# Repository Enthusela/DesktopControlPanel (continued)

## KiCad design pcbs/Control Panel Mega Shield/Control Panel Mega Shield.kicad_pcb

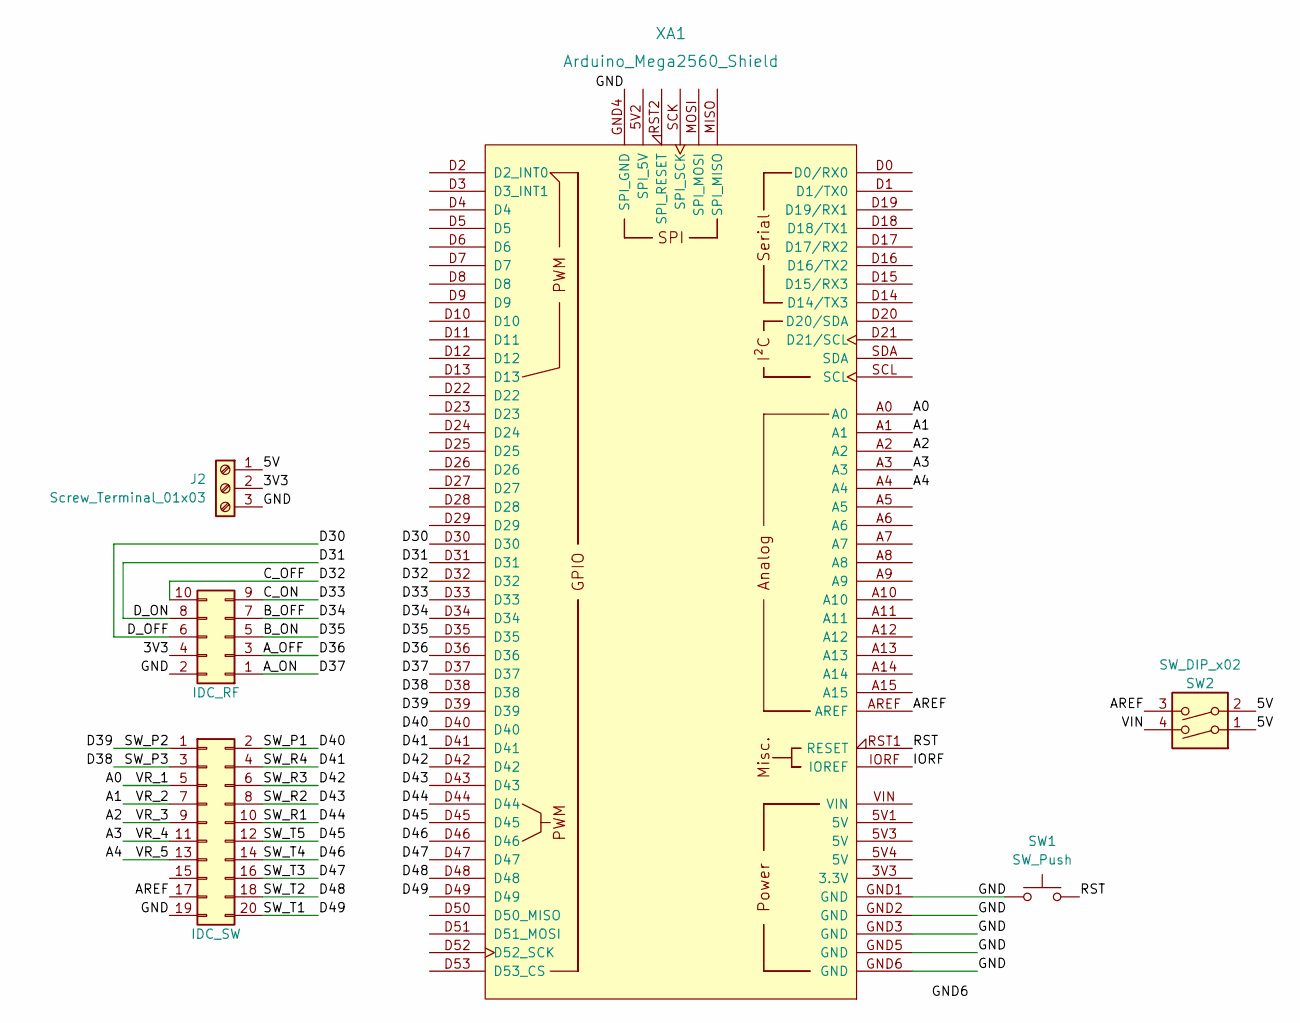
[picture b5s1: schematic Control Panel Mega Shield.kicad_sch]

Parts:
J1: IDC_SW; IDC-Header_2x10_P2.54mm_Vertical
J2: Screw_Terminal_01x03; TerminalBlock_bornier-3_P5.08mm
J3: IDC_RF; IDC-Header_2x05_P2.54mm_Vertical
SW1: SW_Push; SW_PUSH_6mm_H5mm
SW2: SW_DIP_x02; SW_DIP_SPSTx02_Slide_9.78x7.26mm_W7.62mm_P2.54mm
XA1: Arduino_Mega2560_Shield

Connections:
/3V3: J2.2, J3.4
/5V: J2.1, SW2.1, SW2.2
/A0: J1.5, XA1.A0
/A1: J1.7, XA1.A1
/A2: J1.9, XA1.A2
/A3: J1.11, XA1.A3
/A4: J1.13, XA1.A4
/AREF: J1.17, SW2.3, XA1.AREF
/A_OFF: J3.3, XA1.D36
/A_ON: J3.1, XA1.D37
/B_OFF: J3.7, XA1.D34
/B_ON: J3.5, XA1.D35
/C_OFF: J3.10, XA1.D32
/C_ON: J3.9, XA1.D33
/D30: J3.6, XA1.D30
/D31: J3.8, XA1.D31
/D38: J1.3, XA1.D38
/D39: J1.1, XA1.D39
/D40: J1.2, XA1.D40
/D41: J1.4, XA1.D41
/D42: J1.6, XA1.D42
/D43: J1.8, XA1.D43
/D44: J1.10, XA1.D44
/D45: J1.12, XA1.D45
/D46: J1.14, XA1.D46
/D47: J1.16, XA1.D47
/D48: J1.18, XA1.D48
/D49: J1.20, XA1.D49
/GND: J1.19, J2.3, J3.2, SW1.1, XA1.GND1 (GND), XA1.GND2 (GND), XA1.GND3 (GND), XA1.GND4 (SPI_GND), XA1.GND5 (GND), XA1.GND6 (GND)
/IORF: XA1.IORF (IOREF)
/RST: SW1.2, XA1.RST1 (RESET)
/VIN: SW2.4

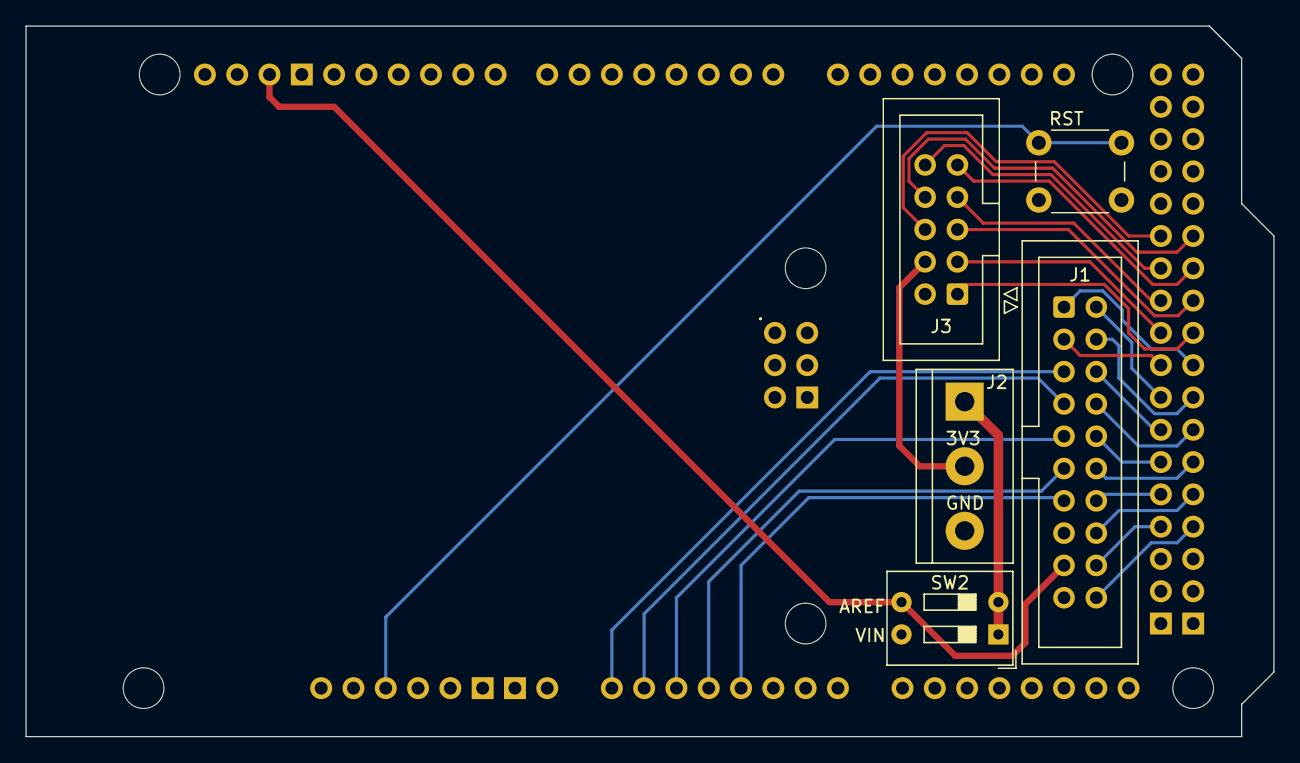
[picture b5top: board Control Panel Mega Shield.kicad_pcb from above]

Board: 2 copper layers, 98.1 x 55.9 mm, 6 parts (0 on the bottom side), 30 nets.

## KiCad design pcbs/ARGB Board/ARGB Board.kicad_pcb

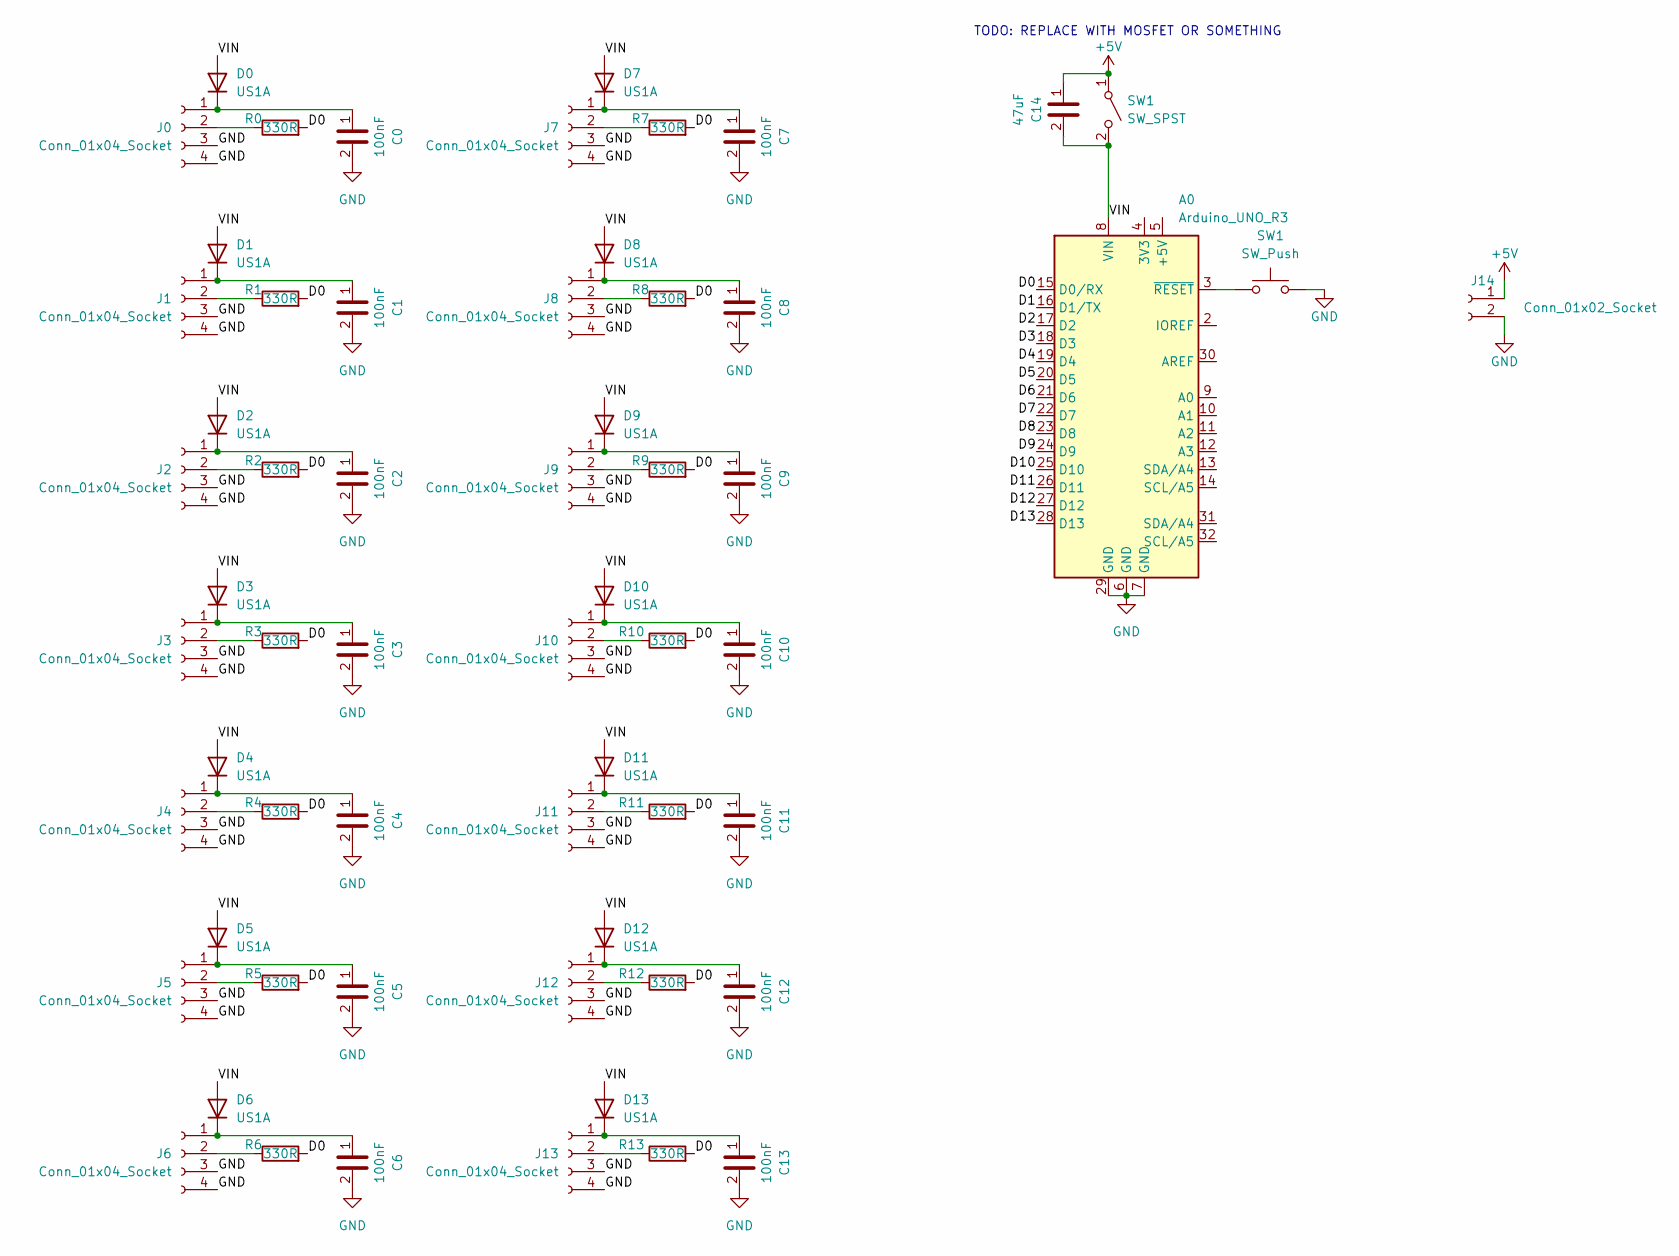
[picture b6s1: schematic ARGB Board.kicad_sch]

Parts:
A0: Arduino_UNO_R3; Arduino_UNO_R3_EdgeCuts
C0, C1, C2, C3, C4, C5, C6, C7, C8, C9, C10, C11, C12, C13: 100nF; C_0805_2012Metric_Pad1.18x1.45mm_HandSolder
C14: 47uF; CP_Radial_D6.3mm_P2.50mm
D0, D1, D2, D3, D4, D5, D6, D7, D8, D9, D10, D11, D12, D13: US1A; D_SMA
J0, J1, J2, J3, J4, J5, J6, J7, J8, J9, J10, J11, J12, J13: Conn_01x04_Socket; PinHeader_1x04_P2.54mm_Vertical
J14: Conn_01x02_Socket; TerminalBlock_bornier-2_P5.08mm
R0, R1, R2, R3, R4, R5, R6, R7, R8, R9, R10, R11, R12, R13: 330R; R_0805_2012Metric
SW1: SW_SPST; SW_E-Switch_EG1271_SPDT

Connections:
/D0: A0.15 (D0/RX), R0.2, R1.2, R2.2, R3.2, R4.2, R5.2, R6.2, R7.2, R8.2, R9.2, R10.2, R11.2, R12.2, R13.2
/D1: A0.16 (D1/TX)
/D2: A0.17 (D2)
/D3: A0.18 (D3)
/D4: A0.19 (D4)
/D5: A0.20 (D5)
/D6: A0.21 (D6)
/D7: A0.22 (D7)
/D8: A0.23 (D8)
/D9: A0.24 (D9)
/D10: A0.25 (D10)
/D11: A0.26 (D11)
/D12: A0.27 (D12)
/D13: A0.28 (D13)
unnamed: C0.1, D0.1 (K), J0.1
unnamed: C1.1, D1.1 (K), J1.1
unnamed: C2.1, D2.1 (K), J2.1
unnamed: C3.1, D3.1 (K), J3.1
unnamed: C4.1, D4.1 (K), J4.1
unnamed: C5.1, D5.1 (K), J5.1
unnamed: C6.1, D6.1 (K), J6.1
unnamed: C7.1, D7.1 (K), J7.1
unnamed: C8.1, D8.1 (K), J8.1
unnamed: C9.1, D9.1 (K), J9.1
unnamed: C10.1, D10.1 (K), J10.1
unnamed: C11.1, D11.1 (K), J11.1
unnamed: C12.1, D12.1 (K), J12.1
unnamed: C13.1, D13.1 (K), J13.1
unnamed: J0.2, R0.1
unnamed: J1.2, R1.1
unnamed: J2.2, R2.1
unnamed: J3.2, R3.1
unnamed: J4.2, R4.1
unnamed: J5.2, R5.1
unnamed: J6.2, R6.1
unnamed: J7.2, R7.1
unnamed: J8.2, R8.1
unnamed: J9.2, R9.1
unnamed: J10.2, R10.1
unnamed: J11.2, R11.1
unnamed: J12.2, R12.1
unnamed: J13.2, R13.1

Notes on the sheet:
TODO: REPLACE WITH MOSFET OR SOMETHING

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
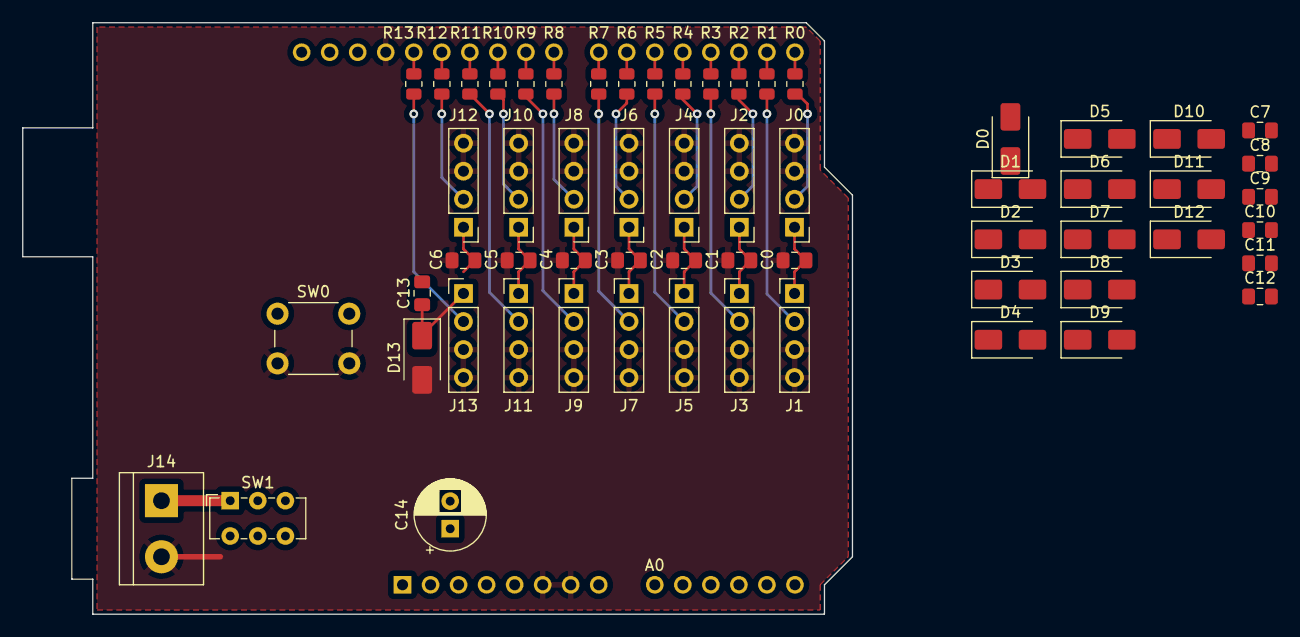
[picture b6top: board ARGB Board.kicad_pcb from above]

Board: 2 copper layers, 75.2 x 53.6 mm, 61 parts (1 on the bottom side), 33 nets.

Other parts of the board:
SW0: SW_Push; SW_PUSH_6mm_H5mm

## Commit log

2023-02-07 Initial commit. Running homepage pset website on local flask.
2023-02-16 Uploaded working files from Raspberry Pi. Webpage is ready for hosting.
2023-02-16 Added app.py and templates folder to staged changes.
2023-02-17 Added package-json files
2023-02-17 Added wordclock e-ink test code
2023-02-17 Added e-ink display wordclock test
2023-02-17 Converted wordclock from folder to submodule
2023-02-17 Updated wordclock files
2023-02-17 Untracked e-ink img folders
2023-02-17 Removed wordclock sub-module
2023-02-17 Added files from successful 7-color e-ink tests
2023-03-16 Bulk commit.
2023-03-17 Added motorised takeover
2023-04-01 Improved timeline. Began converting to node.js.
2023-04-07 Updated Timeline with dynamic thumbnail rendering
2023-10-16 Bulk pre-portfolio commit
2023-10-16 Added missing /audio files
    The original three files appear to be test recordings: the rest were stored in the DCP repo, I believe to save space on my Raspberry Pi, which I now see is unnecessary.
2023-10-16 Merged py folders for PC and raspi
    Raspi scripts for arduino/pc comms and PC scripts for raspi comms/volume control have been merged into one py directory.
2023-10-16 Merged transcript files
    Existing test transcript files have been merged with the complete set from DesktopControlPanel, which were used to generate the content for the website project timeline.
2023-10-16 Added ESPWifiARGBControl code from offline repo
    This logic was developed offline by mistake briefly, and is now being merged into the main repo
2023-10-16 Added RF test code from offline repo
    This logic was tested offline by mistake briefly, and is now being merged into the online repo
2023-10-16 Added archival pre-GitHub files
    These files are earlier versions of code that was eventually duplicated onto github. They appear to be snippets of test code that was later incorporated into "official" code versions at the creation 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
2023-10-16 Added pcbs directory
    Added new directory for the PCB dev files (mostly kicad files)
2023-10-16 Create faceplate directory
    Added faceplate directory as start of move to functionality-based organisation: previously organisation was language-based, which is helpful for code dev work but not so much for hardware.
2023-10-16 Create cabinet dir as root for hardware files
    Created cabinet dir and moved faceplate inside. Added folders for existing dwg and f3d files
2023-10-18 Updated js_test dir to eink
2023-10-18 Updates to dir names, added .gitignore
    Moved "js_test" to "eink" dir after review of contents. Added .gitignore, added KiCad backup dirs to ignore list.
2023-10-18 Reorganised folders based on hardware components
2023-10-18 Reorganised resources for website
    Resources for the website were spread across multiple folders in the root directory: these have now been reconciled in the "website" directory to distinguish them further from the other components of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
    The folders appear to contain duplicate files that will be reconciled in the next commit.
2023-10-18 Consolidated img files in website folder
2023-10-18 Consolidated "AI Journalling" files in website dir
2023-10-18 Relocated eink-only "sh" dir to "eink" dir
2023-10-18 Reorganised "py" dir into relevant feature dirs
2023-10-18 Relocated argb web app files, removed archive dir
    Files from the original web-app test for ARGB control were found in the archive dir: the remaining files were confirmed to be redundant and/or outdated and safe for deletion. This should be the last 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
2023-10-18 Removed audio journal files
    Removed the original audio files from the ai_journal folder as these made up half the size of the repo despite already being transcribed.
2023-10-18 Updated .gitignore
2023-10-18 nodejs now generates img thumbs on server start
2023-10-18 Gallery uses hires in lightbox, otherwise thumbs
2023-10-18 Added missing images to public/images folder
2023-10-19 Renamed website/js to website/node
2023-10-19 Deleted HTML-only web page templates dir
2023-10-19 Added feature_status table
2023-11-30 Progressed to Ivy-focused analysis
    Progressed FitBit feature first analysis. Landed on a different method to analyse the features of the Ivy one by one and relate back to the FitBit features, rather than the other way round.
2025-11-09 Containerised argb_ctrl web app for dev on PC
2025-11-09 Added docker files
2025-11-10 Got ARGB working again. Added test script using uv
2025-11-10 Reorganised argb-test code
2025-11-10 Web app ui now updates values correctly
2026-01-31 Push before reinstalling
